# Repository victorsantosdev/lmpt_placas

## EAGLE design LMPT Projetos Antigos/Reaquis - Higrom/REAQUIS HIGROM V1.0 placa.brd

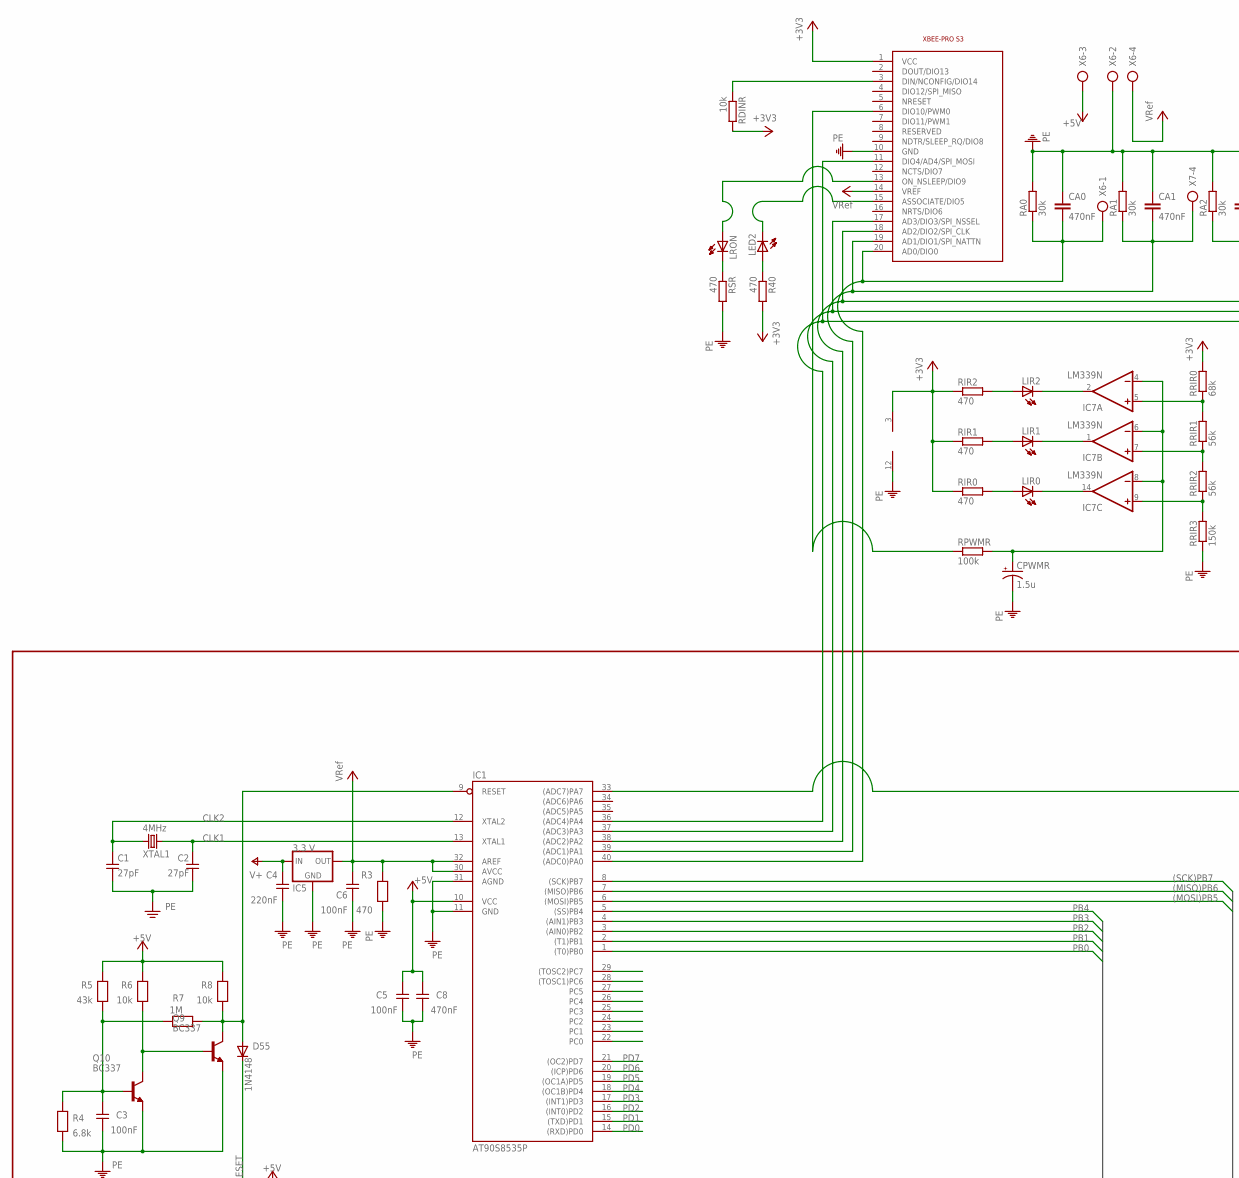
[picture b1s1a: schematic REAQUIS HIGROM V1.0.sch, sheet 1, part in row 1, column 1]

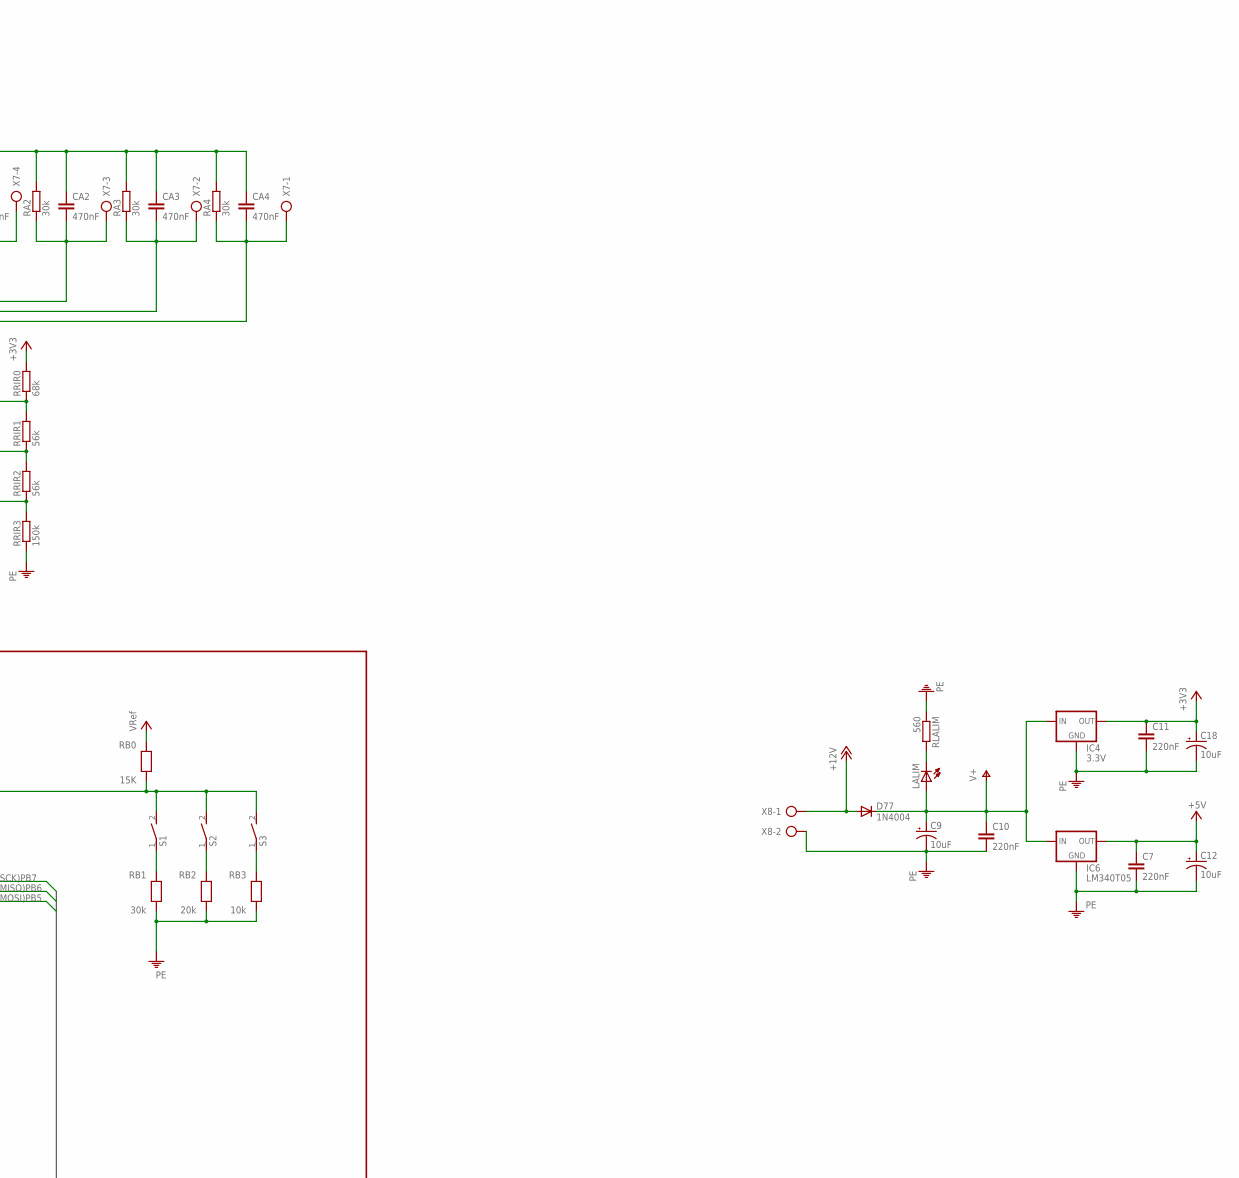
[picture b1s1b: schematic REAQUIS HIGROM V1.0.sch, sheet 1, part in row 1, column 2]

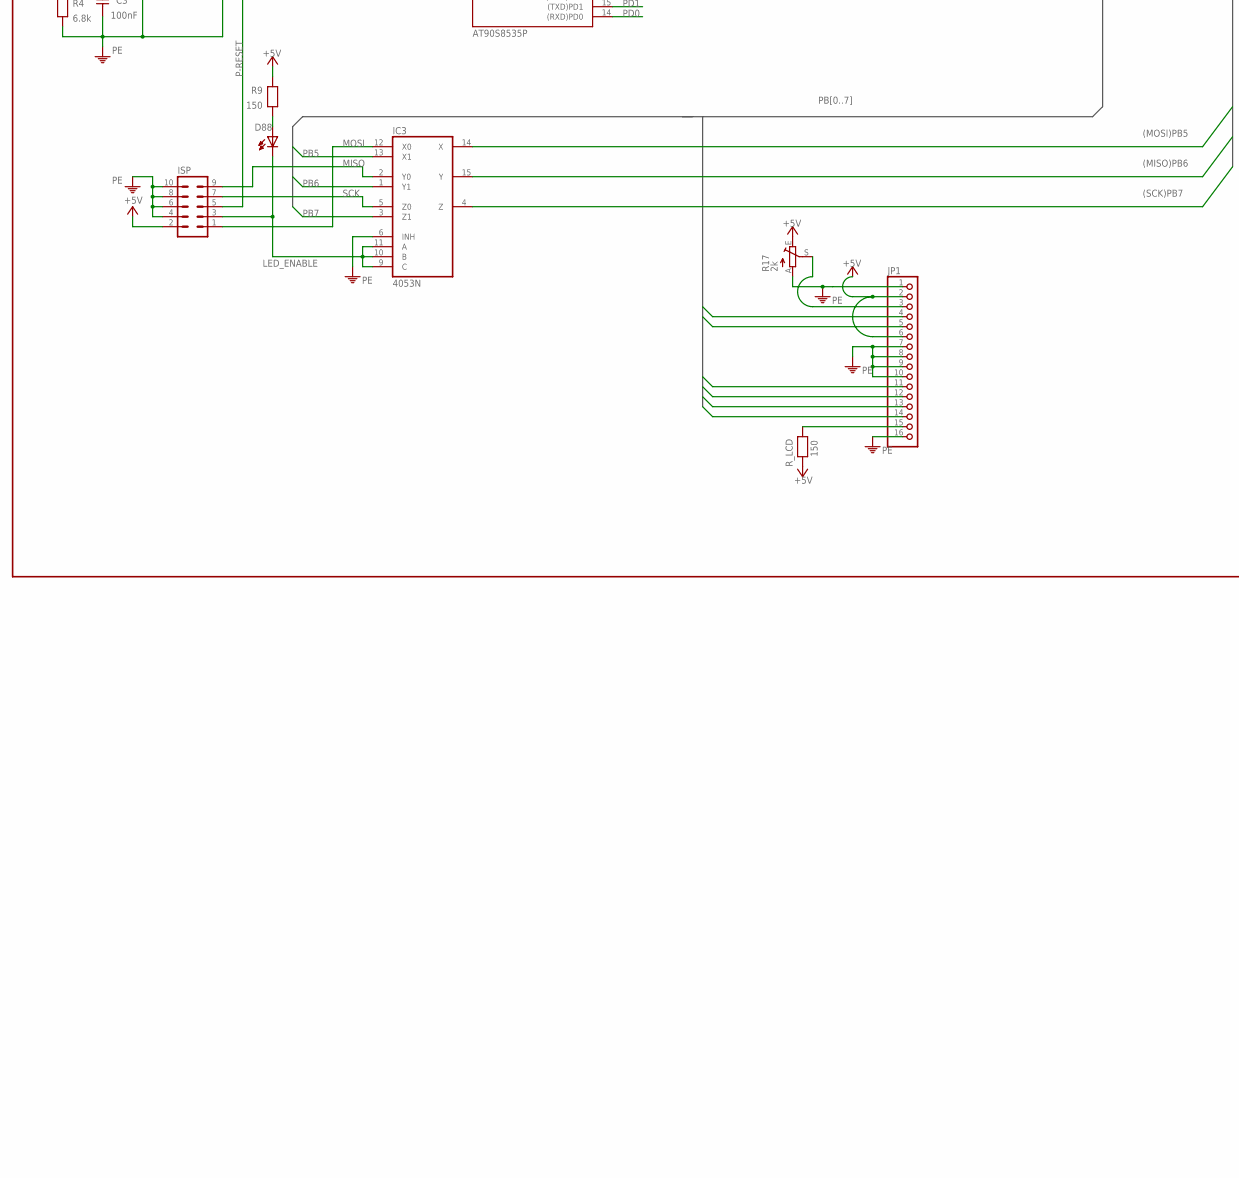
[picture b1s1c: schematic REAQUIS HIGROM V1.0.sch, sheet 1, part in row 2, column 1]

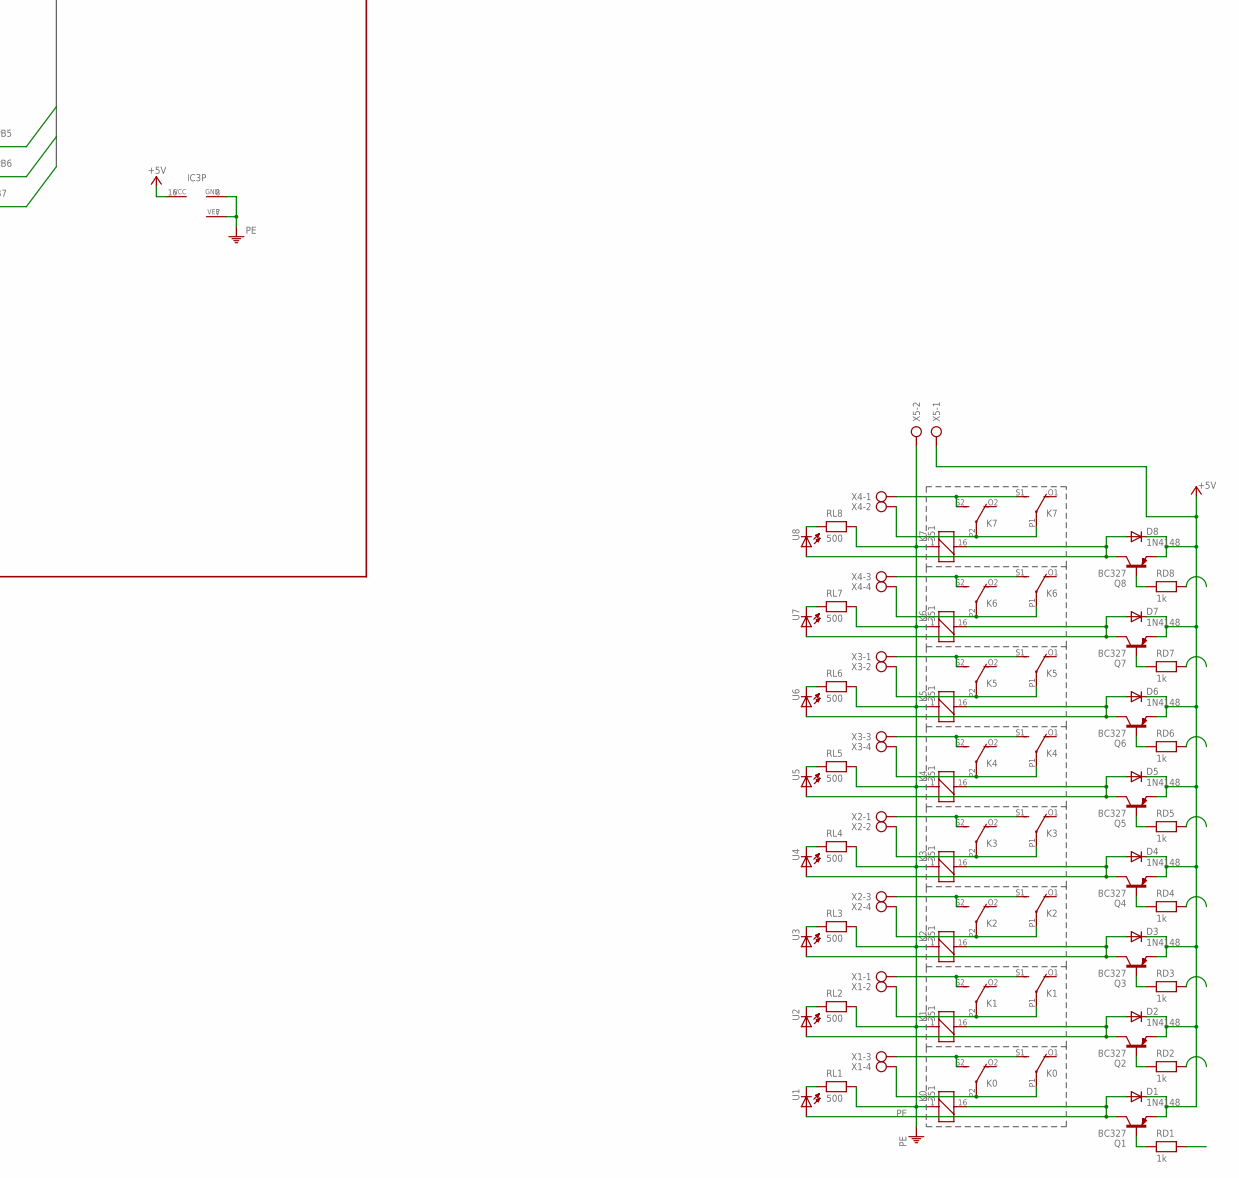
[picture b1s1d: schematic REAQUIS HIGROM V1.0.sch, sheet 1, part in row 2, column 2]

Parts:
C1, C2: 27pF; C-5
C3, C5, C6: 100nF; C-5
C4: 220nF; C-5
C7, C10, C11: 220nF; C5B3.5
C8: 470nF; C-5
C9, C12, C18: 10uF; E2-5
CA0, CA1, CA2, CA3, CA4: 470nF; C5B3.5
CPWMR: 1.5u; E2-5
D1, D2, D3, D4, D5, D6, D7, D8, D55: 1N4148; DO35-10
D77: 1N4004; DO41-10
D88: LED5MM
IC1: AT90S8535P; DIL40
IC3: 4053N; DIL16
IC4: 3.3V; 78XXL
IC5: 3.3 V; 78XXL
IC6: LM340T05; 78XXL
IC7: LM339N; DIL14
ISP: ML10
JP1: PINHD-1X16; 1X16
K0, K1, K2, K3, K4, K5, K6, K7: 351
LALIM: LED5MM
LED2: LED3MM
LIR0, LIR1, LIR2: LED3MM
LRON: LED3MM
Q1, Q2, Q3, Q4, Q5, Q6, Q7, Q8: BC327; TO92-EBC
Q9, Q10: BC337; TO92-EBC
R3: 470; R-10
R4: 6.8k; R-10
R5: 43k; R-10
R6, R8: 10k; R-10
R7: 1M; R-10
R9: 150; R-10
R17: 2k; RJ9W
R40: 470; 0207/7
RA0, RA1, RA2, RA3, RA4: 30k; 0207/7
RB0: 15K; R-10
RB1: 30k; R-10
RB2: 20k; R-10
RB3: 10k; R-10
RD1, RD2, RD3, RD4, RD5, RD6, RD7, RD8: 1k; R-10
RDINR: 10k; 0207/7
RIR0, RIR1, RIR2: 470; 0207/7
RL1, RL2, RL3, RL4, RL5, RL6, RL7, RL8: 500; R-10
RLALIM: 560; 0207/7
RPWMR: 100k; 0207/7
RRIR0: 68k; 0207/7
RRIR1, RRIR2: 56k; 0207/7
RRIR3: 150k; 0207/7
RSR: 470; 0207/7
R_LCD: 150; R-10
S1, S2, S3: DS01E; DS-01
U1, U2, U3, U4, U5, U6, U7, U8: LED3MM
U$1: XBEEPRO900; XBEE-PRO
X1, X2, X3, X4, X6, X7: AK500/4-H
X5, X8: AK500/2
XTAL1: 4MHz; HC18U-V

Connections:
(MISO)PB6: IC1.7 ((MISO)PB6), IC3.15 (Y)
(MOSI)PB5: IC1.6 ((MOSI)PB5), IC3.14 (X)
(SCK)PB7: IC1.8 ((SCK)PB7), IC3.4 (Z)
+3V3: C11.1, C18.+, IC4.OUT, IC7.3 (V+), R40.2, RDINR.2, RIR0.1, RIR1.1, RIR2.1, RRIR0.2, U$1.1 (VCC)
+5V: C5.2, C7.1, C8.2, C12.+, D1.C, D2.C, D3.C, D4.C, D5.C, D6.C, D7.C, D8.C, IC1.10 (VCC), IC3.16 (VCC), IC6.OUT, ISP.2, JP1.2, JP1.6, Q1.E, Q2.E, Q3.E, Q4.E, Q5.E, Q6.E, Q7.E, Q8.E, R5.2, R6.2, R8.2, R9.2, R17.E, R_LCD.2, X5.1, X6.3
+12V: D77.A, X8.1
CLK1: C2.2, IC1.13 (XTAL1), XTAL1.2
CLK2: C1.2, IC1.12 (XTAL2), XTAL1.1
DIN: RDINR.1, U$1.3 (DIN/NCONFIG/DIO14)
LED_ENABLE: D88.K (C), IC3.9 (C), IC3.10 (B), IC3.11 (A), ISP.3
LIR2: IC7.2 (OUT), LIR2.K (C)
MISO: IC3.2 (Y0), ISP.9
MOSI: IC3.12 (X0), ISP.1
unnamed: Q9.B, Q10.C, R6.1
unnamed: C3.2, Q10.B, R4.2, R5.1, R7.1
unnamed: Q8.B, RD8.1
unnamed: IC7.1 (OUT), LIR1.K (C)
unnamed: D7.A, K6.16 (2), Q7.C, U7.A
unnamed: Q6.B, RD6.1
unnamed: LRON.K (C), RSR.1
unnamed: LALIM.K (C), RLALIM.2
unnamed: IC7.14 (OUT), LIR0.K (C)
unnamed: D6.A, K5.16 (2), Q6.C, U6.A
unnamed: Q5.B, RD5.1
unnamed: D88.A, R9.1
unnamed: D5.A, K4.16 (2), Q5.C, U5.A
unnamed: Q4.B, RD4.1
unnamed: D4.A, K3.16 (2), Q4.C, U4.A
unnamed: Q3.B, RD3.1
unnamed: D3.A, K2.16 (2), Q3.C, U3.A
unnamed: Q2.B, RD2.1
unnamed: K0.P1, K0.P2, X1.4
unnamed: K1.P1, K1.P2, X1.2
unnamed: K2.P1, K2.P2, X2.4
unnamed: K3.P1, K3.P2, X2.2
unnamed: K4.P1, K4.P2, X3.4
unnamed: K5.P1, K5.P2, X3.2
unnamed: K6.P1, K6.P2, X4.4
unnamed: K7.P1, K7.P2, X4.2
unnamed: K7.S1 (S), K7.S2 (S), X4.1
unnamed: JP1.15, R_LCD.1
unnamed: K5.S1 (S), K5.S2 (S), X3.1
unnamed: K4.S1 (S), K4.S2 (S), X3.3
unnamed: K3.S1 (S), K3.S2 (S), X2.1
unnamed: K2.S1 (S), K2.S2 (S), X2.3
unnamed: K1.S1 (S), K1.S2 (S), X1.1
unnamed: K0.S1 (S), K0.S2 (S), X1.3
unnamed: K6.S1 (S), K6.S2 (S), X4.3
unnamed: JP1.3, R17.S
unnamed: IC1.33 ((ADC7)PA7), RB0.1, S1.2, S2.2, S3.2
unnamed: RB1.2, S1.1
unnamed: RB2.2, S2.1
unnamed: RB3.2, S3.1
unnamed: CA0.2, IC1.40 ((ADC0)PA0), RA0.1, U$1.20 (AD0/DIO0), X6.1
unnamed: CA1.2, IC1.39 ((ADC1)PA1), RA1.1, U$1.19 (AD1/DIO1/SPI_NATTN), X7.4
unnamed: CA2.2, IC1.38 ((ADC2)PA2), RA2.1, U$1.18 (AD2/DIO2/SPI_CLK), X7.3
unnamed: CA3.2, IC1.37 ((ADC3)PA3), RA3.1, U$1.17 (AD3/DIO3/SPI_NSSEL), X7.2
unnamed: D8.A, K7.16 (2), Q8.C, U8.A
unnamed: CA4.2, IC1.36 ((ADC4)PA4), RA4.1, U$1.11 (DIO4/AD4/SPI_MOSI), X7.1
unnamed: Q7.B, RD7.1
unnamed: LIR0.A, RIR0.2
unnamed: LIR1.A, RIR1.2
unnamed: LIR2.A, RIR2.2
unnamed: IC7.5 (+IN), RRIR0.1, RRIR1.2
unnamed: IC7.7 (+IN), RRIR1.1, RRIR2.2
unnamed: IC7.9 (+IN), RRIR2.1, RRIR3.2
unnamed: CPWMR.+, IC7.4 (-IN), IC7.6 (-IN), IC7.8 (-IN), RPWMR.2
unnamed: LRON.A, U$1.13 (ON_NSLEEP/DIO9)
unnamed: RPWMR.1, U$1.6 (DIO10/PWM0)
unnamed: LED2.K (C), U$1.15 (ASSOCIATE/DIO5)
unnamed: LED2.A, R40.1
unnamed: D2.A, K1.16 (2), Q2.C, U2.A
unnamed: Q1.B, RD1.1
unnamed: D1.A, K0.16 (2), Q1.C, U1.A
unnamed: RL1.1, U1.K (C)
unnamed: RL8.1, U8.K (C)
unnamed: RL7.1, U7.K (C)
unnamed: RL6.1, U6.K (C)
unnamed: RL5.1, U5.K (C)
unnamed: RL4.1, U4.K (C)
unnamed: RL3.1, U3.K (C)
unnamed: RL2.1, U2.K (C)
P-RESET: D55.C, ISP.5
PB0: IC1.1 ((T0)PB0), JP1.5
PB1: IC1.2 ((T1)PB1), JP1.4
PB2: IC1.3 ((AIN0)PB2)
PB3: IC1.4 ((AIN1)PB3)
PB4: IC1.5 ((SS)PB4), JP1.11
PB5: IC3.13 (X1), JP1.12
PB6: IC3.1 (Y1), JP1.13
PB7: IC3.3 (Z1), JP1.14
PC0: IC1.22 (PC0), RD8.2
PC1: IC1.23 (PC1), RD7.2
PC2: IC1.24 (PC2), RD6.2
PC3: IC1.25 (PC3), RD5.2
PC4: IC1.26 (PC4), RD4.2
PC5: IC1.27 (PC5), RD3.2
PC6: IC1.28 ((TOSC1)PC6), RD2.2
PC7: IC1.29 ((TOSC2)PC7), RD1.2
PE: C1.1, C2.1, C3.1, C4.1, C5.1, C6.1, C7.2, C8.1, C9.-, C10.2, C11.2, C12.-, C18.-, CA0.1, CA1.1, CA2.1, CA3.1, CA4.1, CPWMR.-, IC1.11 (GND), IC1.31 (AGND), IC3.6 (INH), IC3.7 (VEE), IC3.8 (GND), IC4.GND, IC5.GND, IC6.GND, IC7.12 (GND), ISP.4, ISP.6, ISP.8, ISP.10, JP1.1, JP1.7, JP1.8, JP1.9, JP1.10, JP1.16, K0.1, K1.1, K2.1, K3.1, K4.1, K5.1, K6.1, K7.1, Q9.E, Q10.E, R3.1, R4.1, R17.A, RA0.2, RA1.2, RA2.2, RA3.2, RA4.2, RB1.1, RB2.1, RB3.1, RL1.2, RL2.2, RL3.2, RL4.2, RL5.2, RL6.2, RL7.2, RL8.2, RLALIM.1, RRIR3.1, RSR.2, U$1.10 (GND), X5.2, X6.2, X8.2
RST: D55.A, IC1.9 (RESET), Q9.C, R7.2, R8.1
SCK: IC3.5 (Z0), ISP.7
V+: C4.2, C9.+, C10.1, D77.C, IC4.IN, IC5.IN, IC6.IN, LALIM.A
VCC: C6.2, IC1.30 (AVCC), IC1.32 (AREF), IC5.OUT, R3.2, RB0.2, U$1.14 (VREF), X6.4

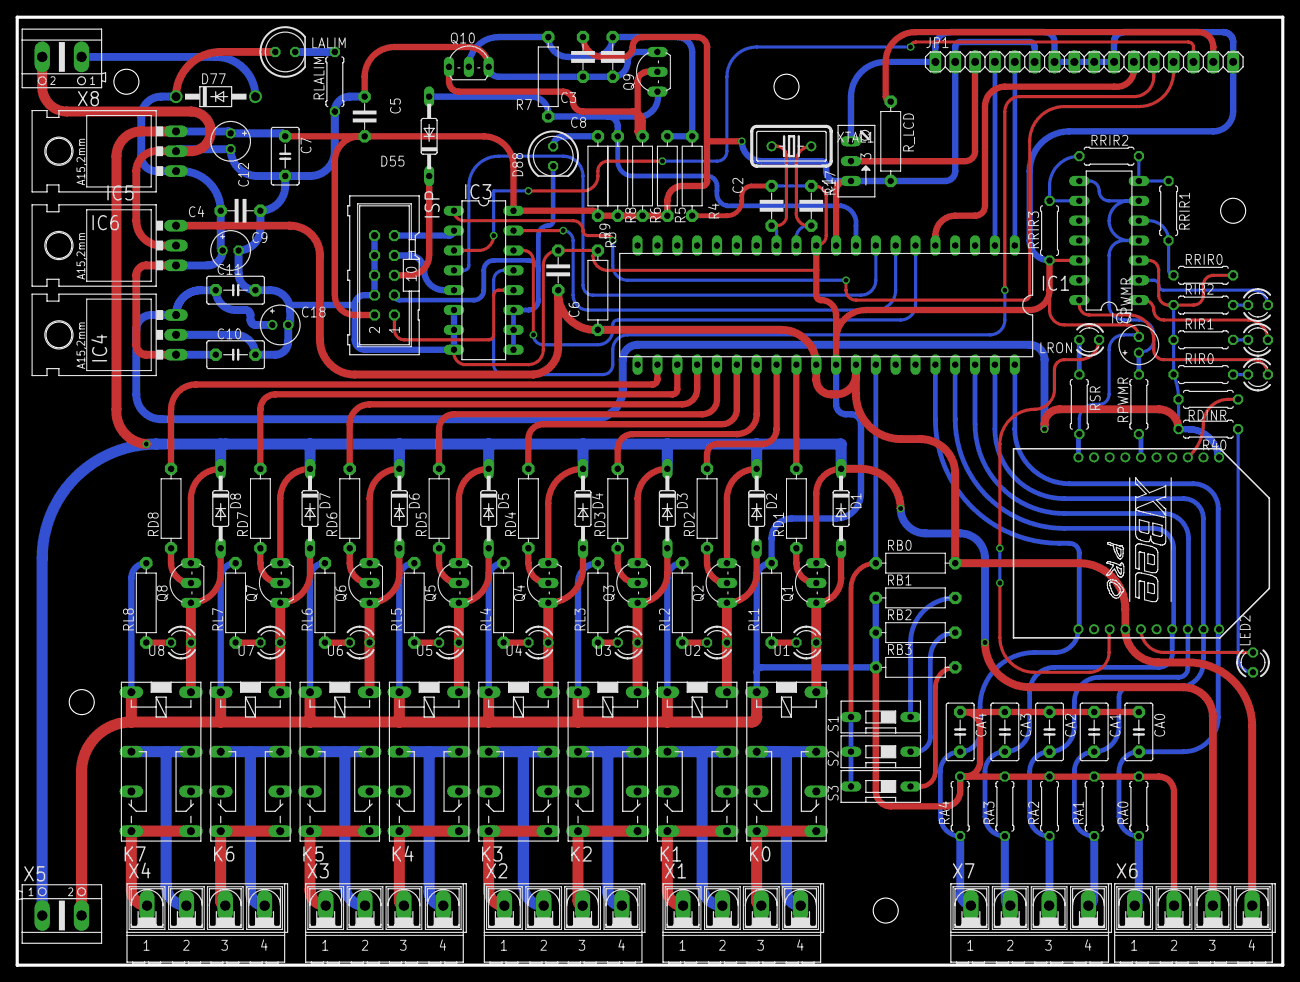
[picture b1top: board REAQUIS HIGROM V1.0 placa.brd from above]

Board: 2 copper layers, 161.9 x 121.3 mm, 129 parts (0 on the bottom side), 102 nets.
